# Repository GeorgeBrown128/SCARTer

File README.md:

# SCARTer
Over-engineering a multi-way SCART source switcher for retro consoles.

Note this project is currently in active development.

A 12-input, 3-output SCART RGB crosspoint switch. Designed to deliver signals from an array of consoles to the two TVs and a capture card in my retro games setup.

The system can copy the signal from any one source to all three outputs without loss of signal integrity, or send different inputs to each output, or any combination inbetween.

Switching is performed by the [FMS6501 12x9 video switch matrix IC](http://www.onsemi.com/PowerSolutions/product.do?id=FMS6501  "Chip data page"). The system is controlled by two ATMEGA328s, one in the remote switching matrix and another in user input control box.

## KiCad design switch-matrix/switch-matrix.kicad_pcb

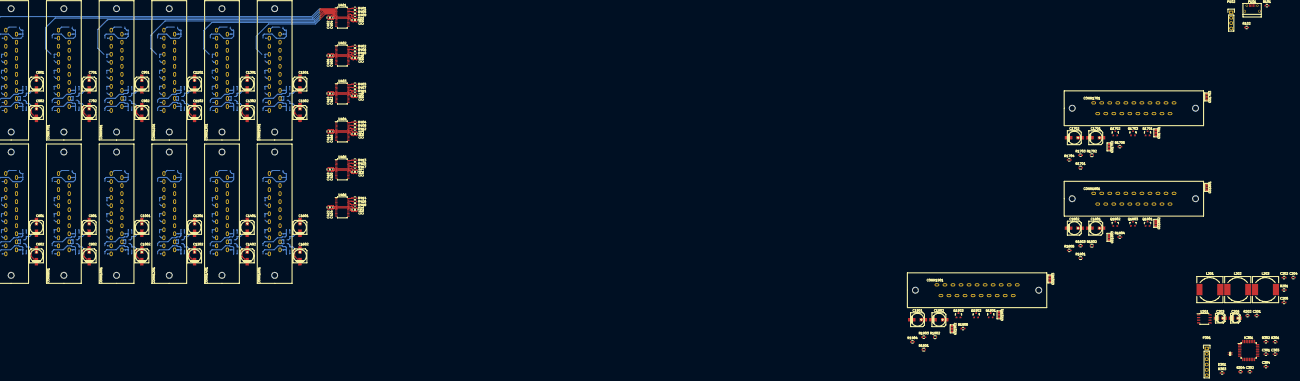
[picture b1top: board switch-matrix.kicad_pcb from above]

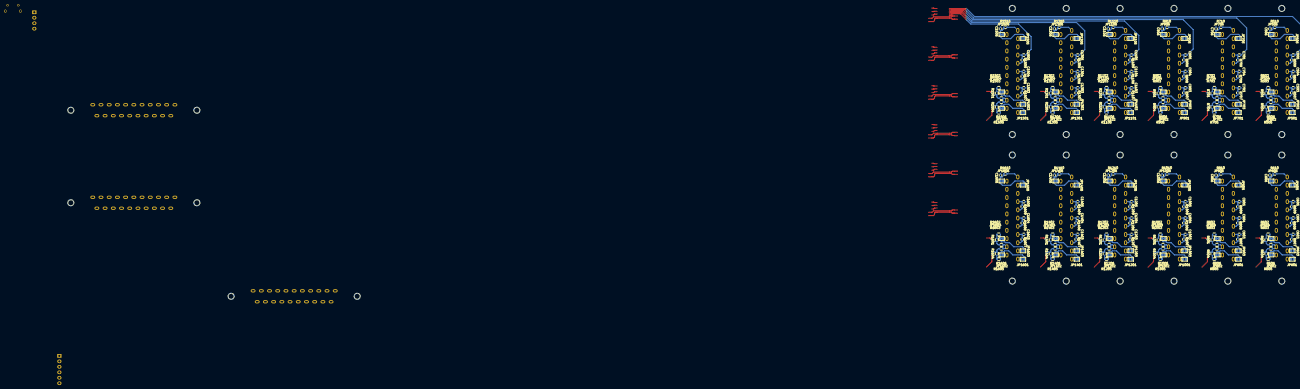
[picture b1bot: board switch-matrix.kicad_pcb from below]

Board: 2 copper layers, 393 parts (240 on the bottom side), 322 nets.

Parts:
C201, C205: 220n; C_0603
C202, C204, C302, C303, C403, C404, C407, C408, C411, C412, C415, C416, C419, C420, C423, C424, C503, C504, C505, C506, C603, C604, C605, C606, C703, C704, C705, C706, C803, C804, C805, C806, C903, C904, C905, C906, C1003, C1004, C1005, C1006, C1103, C1104, C1105, C1106, C1203, C1204, C1205, C1206, C1303, C1304, C1305, C1306, C1403, C1404, C1405, C1406, C1503, C1504, C1505, C1506, C1603, C1604, C1605, C1606: 100n; C_0603
C203, C206: 4.7u; c_elec_4x5.7
C301, C304, C401, C402, C405, C406, C409, C410, C413, C414, C417, C418, C421, C422: 1u; C_0603
C501, C502, C601, C602, C701, C702, C801, C802, C901, C902, C1001, C1002, C1101, C1102, C1201, C1202, C1301, C1302, C1401, C1402, C1501, C1502, C1601, C1602, C1701, C1702, C1801, C1802, C1901, C1902: 220u; c_elec_6.3x7.7
CONN501, CONN601, CONN701, CONN801, CONN901, CONN1001, CONN1101, CONN1201, CONN1301, CONN1401, CONN1501, CONN1601, CONN1701, CONN1801, CONN1901: SCART_Conn; V_SCART
D301: LED_BI; 0605LEDDual
GS1701, GS1702, GS1703, GS1801, GS1802, GS1803, GS1901, GS1902, GS1903: GS3
IC301: ATMEGA328P-A; TQFP-32_7x7mm_Pitch0.8mm
JP501, JP503, JP505, JP601, JP603, JP605, JP701, JP703, JP705, JP801, JP803, JP805, JP901, JP903, JP905, JP1001, JP1003, JP1005, JP1101, JP1103, JP1105, JP1201, JP1203, JP1205, JP1301, JP1303, JP1305, JP1401, JP1403, JP1405, JP1501, JP1503, JP1505, JP1601, JP1603, JP1605: Jumper_NO_Small; GS2
JP502, JP504, JP506, JP602, JP604, JP606, JP702, JP704, JP706, JP802, JP804, JP806, JP902, JP904, JP906, JP1002, JP1004, JP1006, JP1102, JP1104, JP1106, JP1202, JP1204, JP1206, JP1302, JP1304, JP1306, JP1402, JP1404, JP1406, JP1502, JP1504, JP1506, JP1602, JP1604, JP1606: Jumper_NC_Small; GS2
L201, L202, L203: 100u; Neosid_Inductor_SM-NE127
P101: USB_OTG; USB_Micro-B
P102: CONN_01X04; Pin_Header_Straight_1x04
P301: CONN_01X06; Pin_Header_Straight_1x06
Q1701, Q1801, Q1901: BSS84; SOT-23
Q1702, Q1703, Q1802, Q1803, Q1902, Q1903: MMBT3904; SOT-23
R101, R102: 4k7; C_0603
R201, R202, R301, R302, R1704, R1705, R1804, R1805, R1904, R1905: 10k; C_0603
R303, R304: 470; C_0603
R401, R402, R403, R404, R405, R406, R407, R408, R409, R410, R411, R412, R413, R414, R415, R416, R417, R418, R507, R508, R509, R510, R607, R608, R609, R610, R707, R708, R709, R710, R807, R808, R809, R810, R907, R908, R909, R910, R1007, R1008, R1009, R1010, R1107, R1108, R1109, R1110, R1207, R1208, R1209, R1210, R1307, R1308, R1309, R1310, R1407, R1408, R1409, R1410, R1507, R1508, R1509, R1510, R1607, R1608, R1609, R1610, R1703, R1803, R1903: 75; C_0603
R501, R502, R503, R504, R505, R506, R601, R602, R603, R604, R605, R606, R701, R702, R703, R704, R705, R706, R801, R802, R803, R804, R805, R806, R901, R902, R903, R904, R905, R906, R1001, R1002, R1003, R1004, R1005, R1006, R1101, R1102, R1103, R1104, R1105, R1106, R1201, R1202, R1203, R1204, R1205, R1206, R1301, R1302, R1303, R1304, R1305, R1306, R1401, R1402, R1403, R1404, R1405, R1406, R1501, R1502, R1503, R1504, R1505, R1506, R1601, R1602, R1603, R1604, R1605, R1606: 10k; R_0603
R1701, R1702, R1801, R1802, R1901, R1902: 75; R_0603
U201: ST662AC; SOIC-8_3.9x4.9mm_Pitch1.27mm
U401, U402, U403, U404, U405, U406: FMS6501A; TSSOP-28_4.4x9.7mm_Pitch0.65mm

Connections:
6Vbias: Q1702.1, Q1802.1, Q1902.1, R201.2, R202.1
+5V: C204.1, C301.1, C302.1, C303.1, IC301.4, IC301.6, IC301.18, L201.1, L202.1, L203.2, P102.3, P301.1, R101.1, R102.1, R301.1, R302.1
+5VA: C401.1, C402.1, C403.1, C404.1, C405.1, C406.1, C407.1, C408.1, C409.1, C410.1, C411.1, C412.1, C413.1, C414.1, C415.1, C416.1, C417.1, C418.1, C419.1, C420.1, C421.1, C422.1, C423.1, C424.1, L201.2, U401.7, U401.22, U402.7, U402.22, U403.7, U403.22, U404.7, U404.22, U405.7, U405.22, U406.7, U406.22
+5VP: C202.2, C206.1, L202.2, U201.5
+12V: C202.1, C203.1, Q1701.2, Q1702.3, Q1801.2, Q1802.3, Q1901.2, Q1902.3, R201.1, R1704.1, R1804.1, R1904.1, U201.6
/in-mux/AOR_CAP: C1901.1, R417.1
/in-mux/AOR_CRT: C1701.1, R413.1
/in-mux/AOR_LCD: C1801.1, R415.1
/in-mux/SCL: IC301.28, R101.2, U401.16, U402.16, U403.16, U404.16, U405.16, U406.16
/in-mux/SDA: IC301.27, R102.2, U401.17, U402.17, U403.17, U404.17, U405.17, U406.17
/in-mux/SEL_AOL: IC301.10, U406.15
/in-mux/SEL_B: IC301.2, U403.15
/in-mux/SEL_C: IC301.9, U404.15
/in-mux/SEL_G: IC301.1, U402.15
/in-mux/SEL_R: IC301.32, U401.15
/in-mux/scart_in_1/AO_Left: C502.1, U406.1
/in-mux/scart_in_1/AO_Right: C501.1, U405.1
/in-mux/scart_in_1/Blue: C503.1, U403.1
/in-mux/scart_in_1/Composite: C506.1, U404.1
/in-mux/scart_in_1/Green: C504.1, U402.1
/in-mux/scart_in_1/Red: C505.1, U401.1
/in-mux/scart_in_2/AO_Left: C602.1, U406.2
/in-mux/scart_in_2/AO_Right: C601.1, U405.2
/in-mux/scart_in_2/Blue: C603.1, U403.2
/in-mux/scart_in_2/Composite: C606.1, U404.2
/in-mux/scart_in_2/Green: C604.1, U402.2
/in-mux/scart_in_2/Red: C605.1, U401.9
/in-mux/scart_in_3/AO_Left: C702.1, U406.3
/in-mux/scart_in_3/AO_Right: C701.1, U405.3
/in-mux/scart_in_3/Blue: C703.1, U403.3
/in-mux/scart_in_3/Composite: C706.1, U404.3
/in-mux/scart_in_3/Green: C704.1, U402.3
/in-mux/scart_in_3/Red: C705.1, U401.2
/in-mux/scart_in_4/AO_Left: C802.1, U406.4
/in-mux/scart_in_4/AO_Right: C801.1, U405.4
/in-mux/scart_in_4/Blue: C803.1, U403.4
/in-mux/scart_in_4/Composite: C806.1, U404.4
/in-mux/scart_in_4/Green: C804.1, U402.4
/in-mux/scart_in_4/Red: C805.1, U401.10
/in-mux/scart_in_5/AO_Left: C1602.1, U406.14
/in-mux/scart_in_5/AO_Right: C1601.1, U405.14
/in-mux/scart_in_5/Blue: C1603.1, U403.14
/in-mux/scart_in_5/Composite: C1606.1, U404.14
/in-mux/scart_in_5/Green: C1604.1, U402.14
/in-mux/scart_in_5/Red: C1605.1, U401.14
/in-mux/scart_in_6/AO_Left: C902.1, U406.5
/in-mux/scart_in_6/AO_Right: C901.1, U405.5
/in-mux/scart_in_6/Blue: C903.1, U403.5
/in-mux/scart_in_6/Composite: C906.1, U404.5
/in-mux/scart_in_6/Green: C904.1, U402.5
/in-mux/scart_in_6/Red: C905.1, U401.3
/in-mux/scart_in_7/AO_Left: C1002.1, U406.6
/in-mux/scart_in_7/AO_Right: C1001.1, U405.6
/in-mux/scart_in_7/Blue: C1003.1, U403.6
/in-mux/scart_in_7/Composite: C1006.1, U404.6
/in-mux/scart_in_7/Green: C1004.1, U402.6
/in-mux/scart_in_7/Red: C1005.1, U401.11
/in-mux/scart_in_8/AO_Left: C1102.1, U406.9
/in-mux/scart_in_8/AO_Right: C1101.1, U405.9
/in-mux/scart_in_8/Blue: C1103.1, U403.9
/in-mux/scart_in_8/Composite: C1106.1, U404.9
/in-mux/scart_in_8/Green: C1104.1, U402.9
/in-mux/scart_in_8/Red: C1105.1, U401.4
/in-mux/scart_in_9/AO_Left: C1302.1, U406.11
/in-mux/scart_in_9/AO_Right: C1301.1, U405.11
/in-mux/scart_in_9/Blue: C1303.1, U403.11
/in-mux/scart_in_9/Composite: C1306.1, U404.11
/in-mux/scart_in_9/Green: C1304.1, U402.11
/in-mux/scart_in_9/Red: C1305.1, U401.5
/in-mux/scart_in_10/AO_Left: C1502.1, U406.13
/in-mux/scart_in_10/AO_Right: C1501.1, U405.13
/in-mux/scart_in_10/Blue: C1503.1, U403.13
/in-mux/scart_in_10/Composite: C1506.1, U404.13
/in-mux/scart_in_10/Green: C1504.1, U402.13
/in-mux/scart_in_10/Red: C1505.1, U401.6
/in-mux/scart_in_11/AO_Left: C1202.1, U406.10
/in-mux/scart_in_11/AO_Right: C1201.1, U405.10
/in-mux/scart_in_11/Blue: C1203.1, U403.10
/in-mux/scart_in_11/Composite: C1206.1, U404.10
/in-mux/scart_in_11/Green: C1204.1, U402.10
/in-mux/scart_in_11/Red: C1205.1, U401.12
/in-mux/scart_in_12/AO_Left: C1402.1, U406.12
/in-mux/scart_in_12/AO_Right: C1401.1, U405.12
/in-mux/scart_in_12/Blue: C1403.1, U403.12
/in-mux/scart_in_12/Composite: C1406.1, U404.12
/in-mux/scart_in_12/Green: C1404.1, U402.12
/in-mux/scart_in_12/Red: C1405.1, U401.13
/micro/12V_SHDN: IC301.23, R301.2, U201.8
/micro/LED_G: D301.1, IC301.26
/micro/LED_R: D301.3, IC301.25
/micro/SEL_AOL: IC301.11, U405.15
/micro/UART_RX: IC301.30, P102.1
/micro/UART_TX: IC301.31, P102.2
/micro/~RESET: IC301.29, P301.5, R302.2
/psus/VBUS: L203.1, P101.1
/scart_out_1/AL: C1702.1, R414.1
/scart_out_1/ASPECT: CONN1701.8, IC301.15, P301.2, Q1701.3, Q1702.2, Q1703.3, R1705.1
/scart_out_1/B: CONN1701.7, R403.1
/scart_out_1/C: CONN1701.19, GS1703.2, GS1703.3, R404.1
/scart_out_1/G: CONN1701.11, R402.1
/scart_out_1/R: CONN1701.15, R401.1
/scart_out_1/RGB: IC301.12, R1703.1
/scart_out_2/AL: C1802.1, R416.1
/scart_out_2/ASPECT: CONN1801.8, IC301.16, P301.3, Q1801.3, Q1802.2, Q1803.3, R1805.1
/scart_out_2/B: CONN1801.7, R407.1
/scart_out_2/C: CONN1801.19, GS1803.2, GS1803.3, R408.1
/scart_out_2/G: CONN1801.11, R406.1
/scart_out_2/R: CONN1801.15, R405.1
/scart_out_2/RGB: IC301.13, IC301.14, R1803.1
/scart_out_3/AL: C1902.1, R418.1
/scart_out_3/ASPECT: CONN1901.8, IC301.17, P301.4, Q1901.3, Q1902.2, Q1903.3, R1905.1
/scart_out_3/B: CONN1901.7, R411.1
/scart_out_3/C: CONN1901.19, GS1903.2, GS1903.3, R412.1
/scart_out_3/G: CONN1901.11, R410.1
/scart_out_3/R: CONN1901.15, R409.1
GND: C203.2, C204.2, C206.2, C301.2, C302.2, C303.2, C304.2, C401.2, C402.2, C403.2, C404.2, C405.2, C406.2, C407.2, C408.2, C409.2, C410.2, C411.2, C412.2, C413.2, C414.2, C415.2, C416.2, C417.2, C418.2, C419.2, C420.2, C421.2, C422.2, C423.2, C424.2, CONN501.4, CONN501.5, CONN501.9, CONN501.13, CONN501.14, CONN501.17, CONN501.18, CONN501.21, CONN601.4, CONN601.5, CONN601.9, CONN601.13, CONN601.14, CONN601.17, CONN601.18, CONN601.21, CONN701.4, CONN701.5, CONN701.9, CONN701.13, CONN701.14, CONN701.17, CONN701.18, CONN701.21, CONN801.4, CONN801.5, CONN801.9, CONN801.13, CONN801.14, CONN801.17, CONN801.18, CONN801.21, CONN901.4, CONN901.5, CONN901.9, CONN901.13, CONN901.14, CONN901.17, CONN901.18, CONN901.21, CONN1001.4, CONN1001.5, CONN1001.9, CONN1001.13, CONN1001.14, CONN1001.17, CONN1001.18, CONN1001.21, CONN1101.4, CONN1101.5, CONN1101.9, CONN1101.13, CONN1101.14, CONN1101.17, CONN1101.18, CONN1101.21, CONN1201.4, CONN1201.5, CONN1201.9, CONN1201.13, CONN1201.14, CONN1201.17, CONN1201.18, CONN1201.21, CONN1301.4, CONN1301.5, CONN1301.9, CONN1301.13, CONN1301.14, CONN1301.17, CONN1301.18, CONN1301.21, CONN1401.4, CONN1401.5, CONN1401.9, CONN1401.13, CONN1401.14, CONN1401.17, CONN1401.18, CONN1401.21, CONN1501.4, CONN1501.5, CONN1501.9, CONN1501.13, CONN1501.14, CONN1501.17, CONN1501.18, CONN1501.21, CONN1601.4, CONN1601.5, CONN1601.9, CONN1601.13, CONN1601.14, CONN1601.17, CONN1601.18, CONN1601.21, CONN1701.4, CONN1701.5, CONN1701.9, CONN1701.13, CONN1701.14, CONN1701.17, CONN1701.18, CONN1701.21, CONN1801.4, CONN1801.5, CONN1801.9, CONN1801.13, CONN1801.14, CONN1801.17, CONN1801.18, CONN1801.21, CONN1901.4, CONN1901.5, CONN1901.9, CONN1901.13, CONN1901.14, CONN1901.17, CONN1901.18, CONN1901.21, IC301.3, IC301.5, IC301.21, P101.5, P101.6, P102.4, P301.6, Q1703.2, Q1803.2, Q1903.2, R202.2, R303.2, R304.2, R503.2, R506.2, R507.2, R508.2, R509.2, R510.2, R603.2, R606.2, R607.2, R608.2, R609.2, R610.2, R703.2, R706.2, R707.2, R708.2, R709.2, R710.2, R803.2, R806.2, R807.2, R808.2, R809.2, R810.2, R903.2, R906.2, R907.2, R908.2, R909.2, R910.2, R1003.2, R1006.2, R1007.2, R1008.2, R1009.2, R1010.2, R1103.2, R1106.2, R1107.2, R1108.2, R1109.2, R1110.2, R1203.2, R1206.2, R1207.2, R1208.2, R1209.2, R1210.2, R1303.2, R1306.2, R1307.2, R1308.2, R1309.2, R1310.2, R1403.2, R1406.2, R1407.2, R1408.2, R1409.2, R1410.2, R1503.2, R1506.2, R1507.2, R1508.2, R1509.2, R1510.2, R1603.2, R1606.2, R1607.2, R1608.2, R1609.2, R1610.2, R1701.2, R1702.2, R1801.2, R1802.2, R1901.2, R1902.2, U201.7, U401.8, U401.21, U402.8, U402.21, U403.8, U403.21, U404.8, U404.21, U405.8, U405.21, U406.8, U406.21
unnamed: C201.1, U201.1
unnamed: C201.2, U201.2
unnamed: C205.1, U201.3
unnamed: C205.2, U201.4
unnamed: C304.1, IC301.20
unnamed: C501.2, R501.2, R503.1
unnamed: C502.2, R504.2, R506.1
unnamed: C503.2, CONN501.7, R507.1
unnamed: C504.2, CONN501.11, R508.1
unnamed: C505.2, CONN501.15, R509.1
unnamed: C506.2, CONN501.20, JP505.1, JP506.1, JP506.2, R510.1
unnamed: C601.2, R601.2, R603.1
unnamed: C602.2, R604.2, R606.1
unnamed: C603.2, CONN601.7, R607.1
unnamed: C604.2, CONN601.11, R608.1
unnamed: C605.2, CONN601.15, R609.1
unnamed: C606.2, CONN601.20, JP605.1, JP606.1, JP606.2, R610.1
unnamed: C701.2, R701.2, R703.1
unnamed: C702.2, R704.2, R706.1
unnamed: C703.2, CONN701.7, R707.1
unnamed: C704.2, CONN701.11, R708.1
unnamed: C705.2, CONN701.15, R709.1
unnamed: C706.2, CONN701.20, JP705.1, JP706.1, JP706.2, R710.1
unnamed: C801.2, R801.2, R803.1
unnamed: C802.2, R804.2, R806.1
unnamed: C803.2, CONN801.7, R807.1
unnamed: C804.2, CONN801.11, R808.1
unnamed: C805.2, CONN801.15, R809.1
unnamed: C806.2, CONN801.20, JP805.1, JP806.1, JP806.2, R810.1
unnamed: C901.2, R901.2, R903.1
unnamed: C902.2, R904.2, R906.1
unnamed: C903.2, CONN901.7, R907.1
unnamed: C904.2, CONN901.11, R908.1
unnamed: C905.2, CONN901.15, R909.1
unnamed: C906.2, CONN901.20, JP905.1, JP906.1, JP906.2, R910.1
unnamed: C1001.2, R1001.2, R1003.1
unnamed: C1002.2, R1004.2, R1006.1
unnamed: C1003.2, CONN1001.7, R1007.1
unnamed: C1004.2, CONN1001.11, R1008.1
unnamed: C1005.2, CONN1001.15, R1009.1
unnamed: C1006.2, CONN1001.20, JP1005.1, JP1006.1, JP1006.2, R1010.1
unnamed: C1101.2, R1101.2, R1103.1
unnamed: C1102.2, R1104.2, R1106.1
unnamed: C1103.2, CONN1101.7, R1107.1
unnamed: C1104.2, CONN1101.11, R1108.1
unnamed: C1105.2, CONN1101.15, R1109.1
unnamed: C1106.2, CONN1101.20, JP1105.1, JP1106.1, JP1106.2, R1110.1
unnamed: C1201.2, R1201.2, R1203.1
unnamed: C1202.2, R1204.2, R1206.1
unnamed: C1203.2, CONN1201.7, R1207.1
unnamed: C1204.2, CONN1201.11, R1208.1
unnamed: C1205.2, CONN1201.15, R1209.1
unnamed: C1206.2, CONN1201.20, JP1205.1, JP1206.1, JP1206.2, R1210.1
unnamed: C1301.2, R1301.2, R1303.1
unnamed: C1302.2, R1304.2, R1306.1
unnamed: C1303.2, CONN1301.7, R1307.1
unnamed: C1304.2, CONN1301.11, R1308.1
unnamed: C1305.2, CONN1301.15, R1309.1
unnamed: C1306.2, CONN1301.20, JP1305.1, JP1306.1, JP1306.2, R1310.1
unnamed: C1401.2, R1401.2, R1403.1
unnamed: C1402.2, R1404.2, R1406.1
unnamed: C1403.2, CONN1401.7, R1407.1
unnamed: C1404.2, CONN1401.11, R1408.1
unnamed: C1405.2, CONN1401.15, R1409.1
unnamed: C1406.2, CONN1401.20, JP1405.1, JP1406.1, JP1406.2, R1410.1
unnamed: C1501.2, R1501.2, R1503.1
unnamed: C1502.2, R1504.2, R1506.1
unnamed: C1503.2, CONN1501.7, R1507.1
unnamed: C1504.2, CONN1501.11, R1508.1
unnamed: C1505.2, CONN1501.15, R1509.1
unnamed: C1506.2, CONN1501.20, JP1505.1, JP1506.1, JP1506.2, R1510.1
unnamed: C1601.2, R1601.2, R1603.1
unnamed: C1602.2, R1604.2, R1606.1
unnamed: C1603.2, CONN1601.7, R1607.1
unnamed: C1604.2, CONN1601.11, R1608.1
unnamed: C1605.2, CONN1601.15, R1609.1
unnamed: C1606.2, CONN1601.20, JP1605.1, JP1606.1, JP1606.2, R1610.1
unnamed: C1701.2, CONN1701.1, GS1701.2, GS1701.3, R1701.1
unnamed: C1702.2, CONN1701.3, GS1702.2, GS1702.3, R1702.1
unnamed: C1801.2, CONN1801.1, GS1801.2, GS1801.3, R1801.1
unnamed: C1802.2, CONN1801.3, GS1802.2, GS1802.3, R1802.1
unnamed: C1901.2, CONN1901.1, GS1901.2, GS1901.3, R1901.1
unnamed: C1902.2, CONN1901.3, GS1902.2, GS1902.3, R1902.1
unnamed: CONN501.1, JP501.2
unnamed: CONN501.2, JP501.1, JP502.1, JP502.2, R505.1
unnamed: CONN501.3, JP503.2
unnamed: CONN501.6, JP503.1, JP504.1, JP504.2, R502.1
unnamed: CONN501.19, JP505.2
unnamed: CONN601.1, JP601.2
unnamed: CONN601.2, JP601.1, JP602.1, JP602.2, R605.1
unnamed: CONN601.3, JP603.2
unnamed: CONN601.6, JP603.1, JP604.1, JP604.2, R602.1
unnamed: CONN601.19, JP605.2
unnamed: CONN701.1, JP701.2
unnamed: CONN701.2, JP701.1, JP702.1, JP702.2, R705.1
unnamed: CONN701.3, JP703.2
unnamed: CONN701.6, JP703.1, JP704.1, JP704.2, R702.1
unnamed: CONN701.19, JP705.2
unnamed: CONN801.1, JP801.2
unnamed: CONN801.2, JP801.1, JP802.1, JP802.2, R805.1
unnamed: CONN801.3, JP803.2
unnamed: CONN801.6, JP803.1, JP804.1, JP804.2, R802.1
unnamed: CONN801.19, JP805.2
unnamed: CONN901.1, JP901.2
unnamed: CONN901.2, JP901.1, JP902.1, JP902.2, R905.1
unnamed: CONN901.3, JP903.2
unnamed: CONN901.6, JP903.1, JP904.1, JP904.2, R902.1
unnamed: CONN901.19, JP905.2
unnamed: CONN1001.1, JP1001.2
unnamed: CONN1001.2, JP1001.1, JP1002.1, JP1002.2, R1005.1
unnamed: CONN1001.3, JP1003.2
unnamed: CONN1001.6, JP1003.1, JP1004.1, JP1004.2, R1002.1
unnamed: CONN1001.19, JP1005.2
unnamed: CONN1101.1, JP1101.2
unnamed: CONN1101.2, JP1101.1, JP1102.1, JP1102.2, R1105.1
unnamed: CONN1101.3, JP1103.2
unnamed: CONN1101.6, JP1103.1, JP1104.1, JP1104.2, R1102.1
unnamed: CONN1101.19, JP1105.2
unnamed: CONN1201.1, JP1201.2
unnamed: CONN1201.2, JP1201.1, JP1202.1, JP1202.2, R1205.1
unnamed: CONN1201.3, JP1203.2
unnamed: CONN1201.6, JP1203.1, JP1204.1, JP1204.2, R1202.1
unnamed: CONN1201.19, JP1205.2
unnamed: CONN1301.1, JP1301.2
unnamed: CONN1301.2, JP1301.1, JP1302.1, JP1302.2, R1305.1
unnamed: CONN1301.3, JP1303.2
unnamed: CONN1301.6, JP1303.1, JP1304.1, JP1304.2, R1302.1
unnamed: CONN1301.19, JP1305.2
unnamed: CONN1401.1, JP1401.2
unnamed: CONN1401.2, JP1401.1, JP1402.1, JP1402.2, R1405.1
unnamed: CONN1401.3, JP1403.2
unnamed: CONN1401.6, JP1403.1, JP1404.1, JP1404.2, R1402.1
unnamed: CONN1401.19, JP1405.2
unnamed: CONN1501.1, JP1501.2
unnamed: CONN1501.2, JP1501.1, JP1502.1, JP1502.2, R1505.1
unnamed: CONN1501.3, JP1503.2
unnamed: CONN1501.6, JP1503.1, JP1504.1, JP1504.2, R1502.1
unnamed: CONN1501.19, JP1505.2
unnamed: CONN1601.1, JP1601.2
unnamed: CONN1601.2, JP1601.1, JP1602.1, JP1602.2, R1605.1
unnamed: CONN1601.3, JP1603.2
unnamed: CONN1601.6, JP1603.1, JP1604.1, JP1604.2, R1602.1
unnamed: CONN1601.19, JP1605.2
unnamed: CONN1701.2, GS1701.1
unnamed: CONN1701.6, GS1702.1
unnamed: CONN1701.16, R1703.2
unnamed: CONN1701.20, GS1703.1
unnamed: CONN1801.2, GS1801.1
unnamed: CONN1801.6, GS1802.1
unnamed: CONN1801.16, R1803.2
unnamed: CONN1801.20, GS1803.1
unnamed: CONN1901.2, GS1901.1
unnamed: CONN1901.6, GS1902.1
unnamed: CONN1901.16, R1903.2
unnamed: CONN1901.20, GS1903.1
unnamed: D301.2, R304.1
unnamed: D301.4, R303.1
unnamed: P101.2, P101.3
unnamed: Q1701.1, R1704.2
unnamed: Q1703.1, R1705.2
unnamed: Q1801.1, R1804.2
unnamed: Q1803.1, R1805.2
unnamed: Q1901.1, R1904.2
unnamed: Q1903.1, R1905.2
unnamed: R401.2, U401.28
unnamed: R402.2, U402.28
unnamed: R403.2, U403.28
unnamed: R404.2, U404.28
unnamed: R405.2, U401.26
unnamed: R406.2, U402.26
unnamed: R407.2, U403.26
unnamed: R408.2, U404.26
unnamed: R409.2, U401.24
unnamed: R410.2, U402.24
unnamed: R411.2, U403.24
unnamed: R412.2, U404.24
unnamed: R413.2, U405.28
unnamed: R414.2, U406.28
unnamed: R415.2, U405.26
unnamed: R416.2, U406.26
unnamed: R417.2, U405.24
unnamed: R418.2, U406.24
unnamed: R501.1, R502.2
unnamed: R504.1, R505.2
unnamed: R601.1, R602.2
unnamed: R604.1, R605.2
unnamed: R701.1, R702.2
unnamed: R704.1, R705.2
unnamed: R801.1, R802.2
unnamed: R804.1, R805.2
unnamed: R901.1, R902.2
unnamed: R904.1, R905.2
unnamed: R1001.1, R1002.2
unnamed: R1004.1, R1005.2
unnamed: R1101.1, R1102.2
unnamed: R1104.1, R1105.2
unnamed: R1201.1, R1202.2
unnamed: R1204.1, R1205.2
unnamed: R1301.1, R1302.2
unnamed: R1304.1, R1305.2
unnamed: R1401.1, R1402.2
unnamed: R1404.1, R1405.2
unnamed: R1501.1, R1502.2
unnamed: R1504.1, R1505.2
unnamed: R1601.1, R1602.2
unnamed: R1604.1, R1605.2

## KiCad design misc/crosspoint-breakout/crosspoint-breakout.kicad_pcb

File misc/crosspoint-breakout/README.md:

# FMS6501 Breakout Board

A simple breakout board to test the performanmce of the FMS6501.

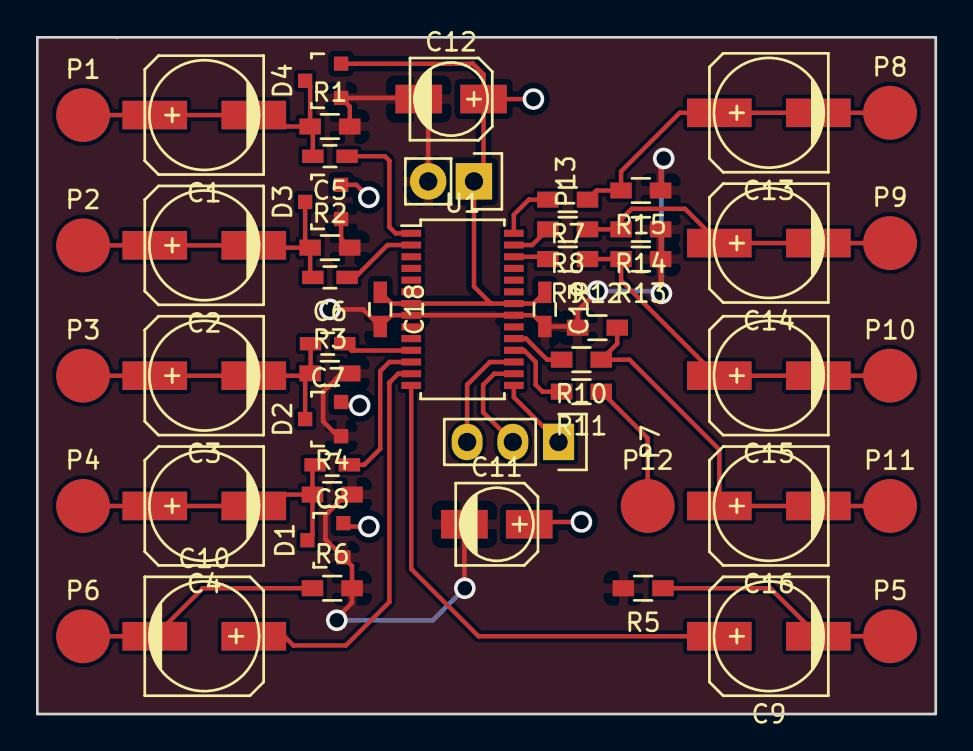
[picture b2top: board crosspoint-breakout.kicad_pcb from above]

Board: 2 copper layers, 49.9 x 37.6 mm, 51 parts (0 on the bottom side), 27 nets.

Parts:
C1, C2, C3, C4, C9, C10, C13, C14, C15, C16: 220u; c_elec_6.3x7.7
C5, C6, C7, C8, C17, C18: 100n; C_0603_HandSoldering
C11, C12: 10u; c_elec_4x5.3
D1, D2, D3, D4: BAV99+; SOT-23
P1, P2, P3, P4, P5, P6: CONN_01X01; Measurement_Point_Round-SMD-Pad_Big
P7: CONN_01X03; Pin_Header_Straight_1x03
P8, P9, P10, P11, P12: pad; Measurement_Point_Round-SMD-Pad_Big
P13: CONN_01X02; Pin_Header_Straight_1x02
R1, R2, R3, R4, R7, R8, R9, R10, R11, R12, R13, R14, R15: 75; R_0603_HandSoldering
R5, R6: 22k; R_0603_HandSoldering
U1: FMS6501A; TSSOP-28_4.4x9.7mm_Pitch0.65mm

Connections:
+5V: C11.1, C12.1, C17.1, C18.1, D1.2, D2.2, D3.2, D4.2, P13.1, U1.7, U1.22
GND: C11.2, C12.2, C17.2, C18.2, D1.1, D2.1, D3.1, D4.1, P13.2, R1.2, R2.2, R3.2, R4.2, R5.2, R6.2, R12.1, R13.1, R14.1, R15.1, U1.8, U1.21
unnamed: C1.1, C1.2, C5.2, D4.3, P1.1, R1.1
unnamed: C2.1, C2.2, C6.2, D3.3, P2.1, R2.1
unnamed: C3.1, C3.2, C7.2, D2.3, P3.1, R3.1
unnamed: C4.1, C4.2, C8.2, D1.3, P4.1, R4.1
unnamed: C5.1, U1.1
unnamed: C6.1, U1.2
unnamed: C7.1, U1.11
unnamed: C8.1, U1.12
unnamed: C9.1, U1.14
unnamed: C9.2, P5.1, R5.1
unnamed: C10.1, U1.13
unnamed: C10.2, P6.1, R6.1
unnamed: C13.1, C13.2, P8.1, R7.1, R15.2
unnamed: C14.1, C14.2, P9.1, R8.1, R14.2
unnamed: C15.1, C15.2, P10.1, R9.1, R13.2
unnamed: C16.1, C16.2, P11.1, R10.1, R12.2
unnamed: P7.1, U1.15
unnamed: P7.2, U1.16
unnamed: P7.3, U1.17
unnamed: P12.1, R11.1
unnamed: R7.2, U1.28
unnamed: R8.2, U1.27
unnamed: R9.2, U1.26
unnamed: R10.2, U1.19
unnamed: R11.2, U1.18

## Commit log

2018-06-27 I should start keeping this project in version control really, so here goes: + Breakout board that was used for initial testing. + Current state of the schematic for the switch matrix. + Component/fo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
2018-07-08 + Add the dual LED footprint. * Got the input scart connector grid sorted with a little layout duplication script.
2018-07-13 + Start the layout * (switching to new OS so need to push this!)
